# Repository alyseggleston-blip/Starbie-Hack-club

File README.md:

# project name starbie hack club half life week one
creating a pcb for the first week of half life
## how it works desktop pet with microcontroller temperature environment sensor a display ans a motion sensor

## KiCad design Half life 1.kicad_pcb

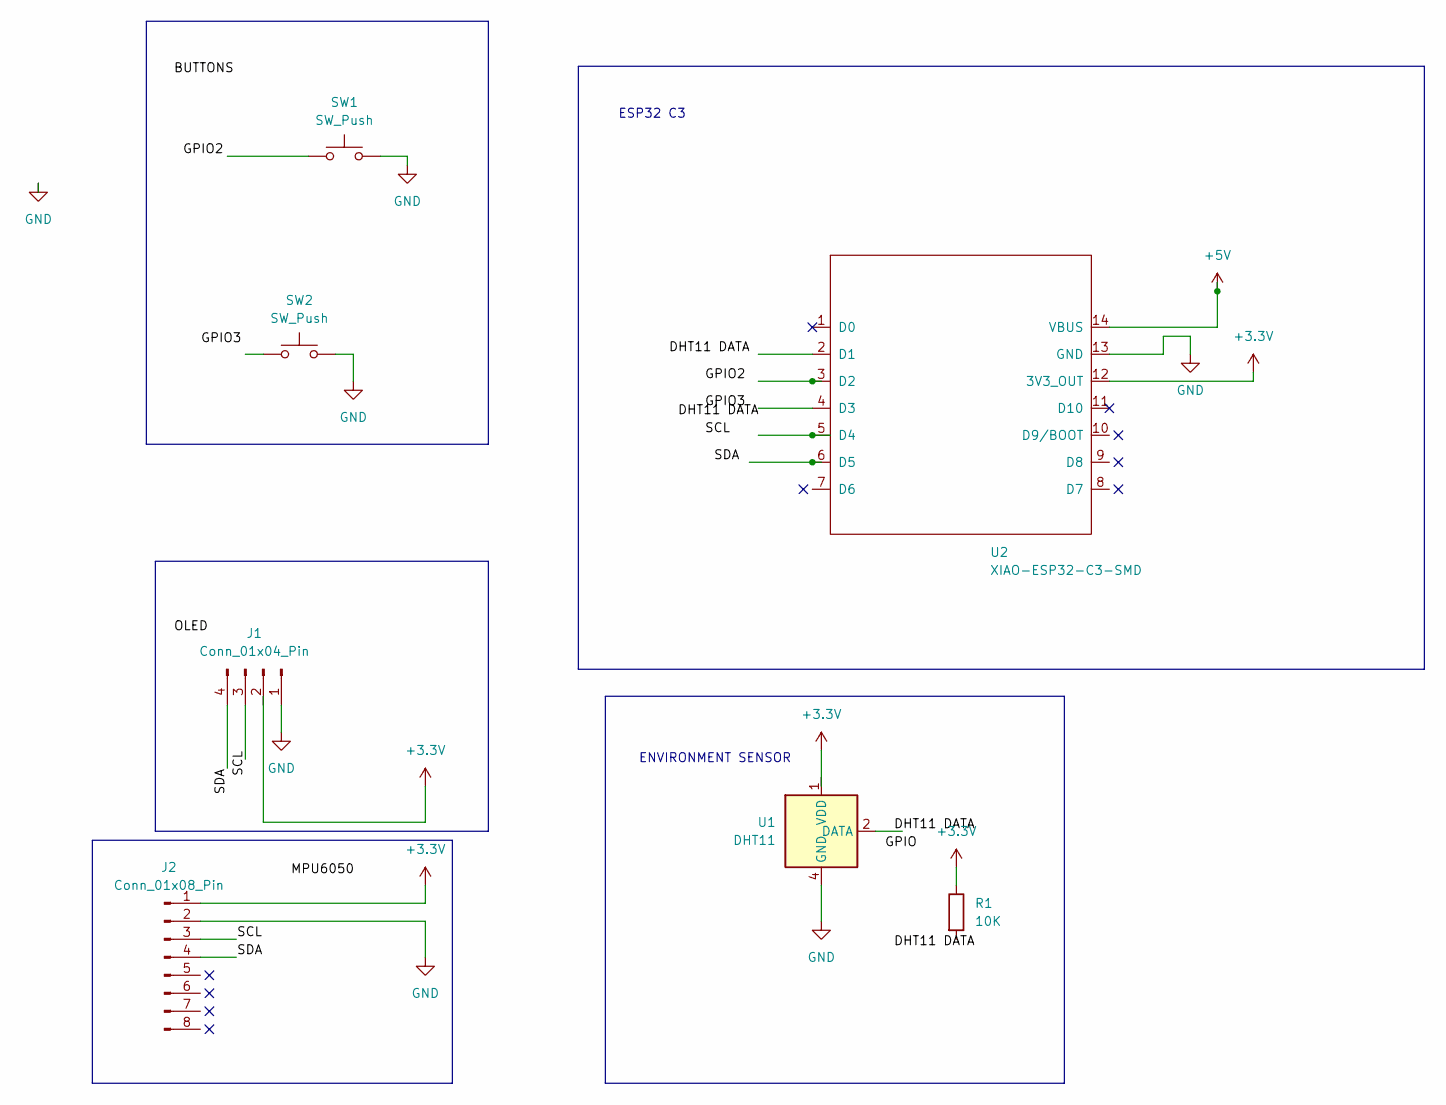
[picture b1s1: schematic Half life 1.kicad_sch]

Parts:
J1: Conn_01x04_Pin; Display_128x64_096_I2C
J2: Conn_01x08_Pin; MPU6050_Module
R1: 10K; R_Axial_DIN0207_L6.3mm_D2.5mm_P7.62mm_Horizontal
SW1, SW2: SW_Push; SW_Cherry_MX_1.00u_PCB
U1: DHT11; Aosong_DHT11_5.5x12.0_P2.54mm
U2: XIAO-ESP32-C3-SMD; XIAO-ESP32-C6-DIP

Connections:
+3.3V: J2.1, R1.1, U2.12 (3V3_OUT)
+5V: U2.14 (VBUS)
/DHT11 DATA: U1.2 (DATA)
/SCL: J1.3, J2.3
/SDA: J1.4, J2.4
GND: J1.1, J2.2, SW1.2 (2_2), SW2.2 (2_2), U1.4 (GND), U2.13 (GND)

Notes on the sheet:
ESP32 C3
ENVIRONMENT SENSOR

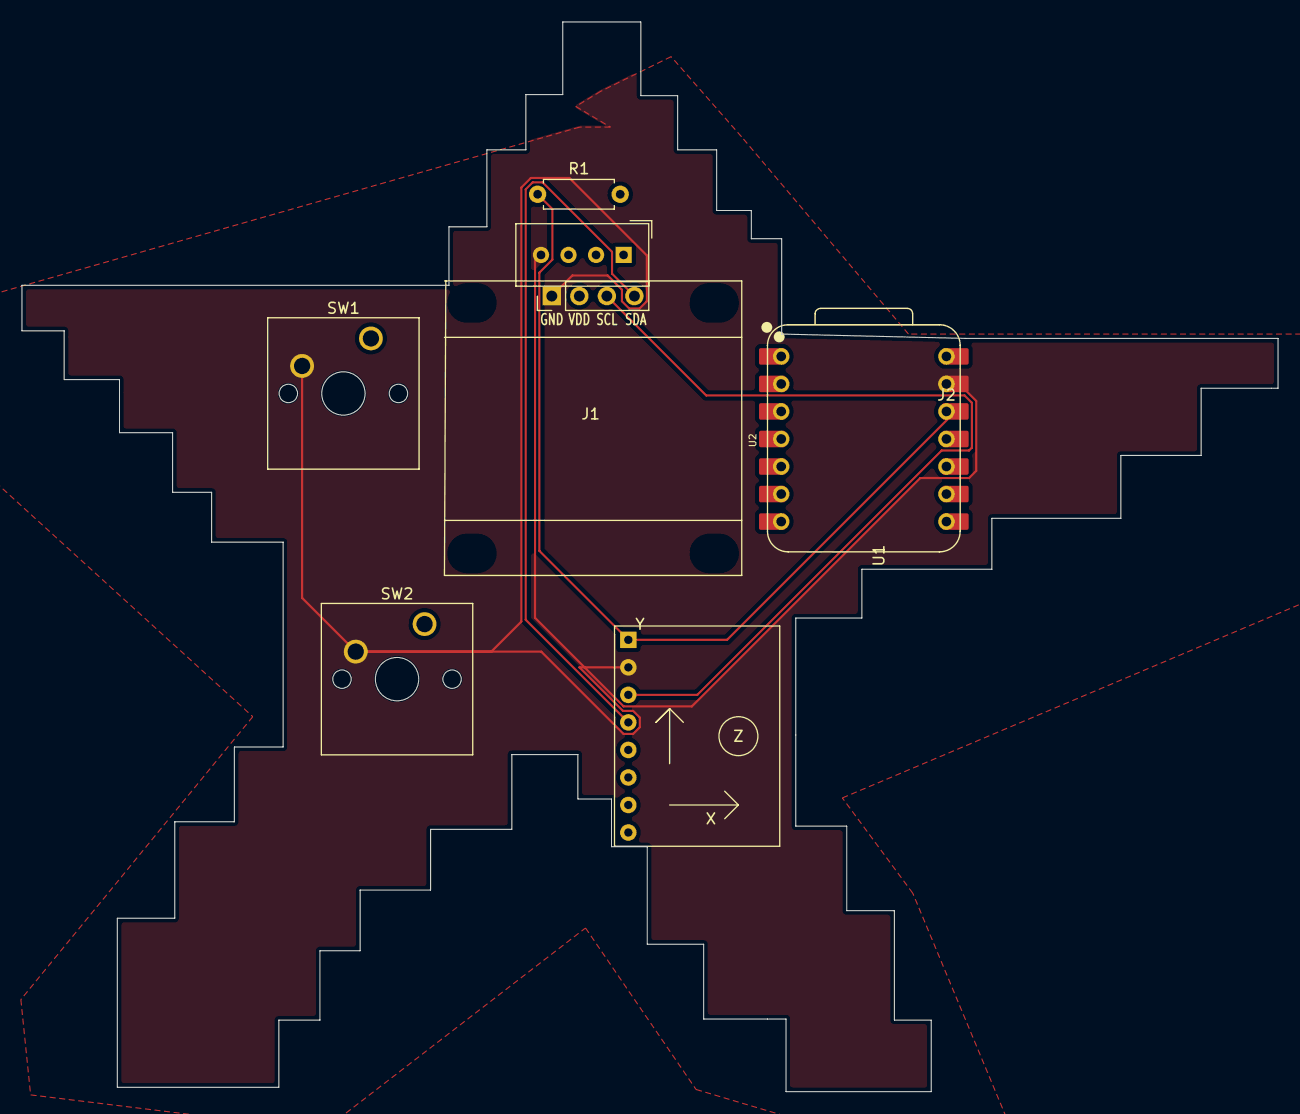
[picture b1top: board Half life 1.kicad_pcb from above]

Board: 2 copper layers, 115.9 x 98.7 mm, 7 parts (0 on the bottom side), 4 nets.
